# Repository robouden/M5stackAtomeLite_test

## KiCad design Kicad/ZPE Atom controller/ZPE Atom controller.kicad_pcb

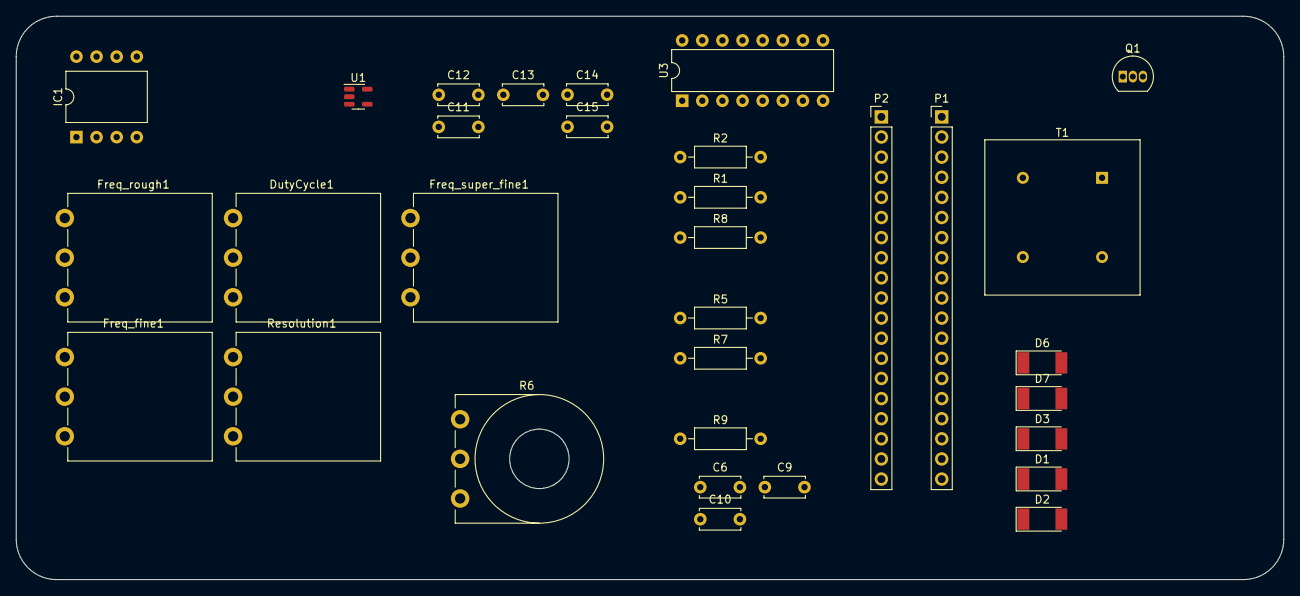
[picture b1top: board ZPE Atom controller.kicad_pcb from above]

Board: 2 copper layers, 160.0 x 71.1 mm, 32 parts (0 on the bottom side), 20 nets, no tracks yet.

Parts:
C6: 1NF 400V; C_Disc_D5.0mm_W2.5mm_P5.00mm
C9, C10, C11, C12, C13, C14, C15: 100nF; C_Disc_D5.0mm_W2.5mm_P5.00mm
D1, D2, D3: D524; D_MELF
D6, D7: 4004; D_MELF
DutyCycle1: 10k; Potentiometer_Piher_PC-16_Single_Vertical
Freq_fine1: 10K; Potentiometer_Piher_PC-16_Single_Vertical
Freq_rough1: 10K; Potentiometer_Piher_PC-16_Single_Vertical
Freq_super_fine1: 10k; Potentiometer_Piher_PC-16_Single_Vertical
IC1: TC4424AVPA; DIP-8_W10.16mm
P1, P2: CONN_01X18; PinHeader_1x19_P2.54mm_Vertical
Q1: PN2222A; TO-92_Inline
R1: 4.7k; R_Axial_DIN0207_L6.3mm_D2.5mm_P10.16mm_Horizontal
R2, R8: 1k; R_Axial_DIN0207_L6.3mm_D2.5mm_P10.16mm_Horizontal
R5: 1K; R_Axial_DIN0207_L6.3mm_D2.5mm_P10.16mm_Horizontal
R6: 100; Potentiometer_Piher_T-16L_Single_Vertical_Hole
R7, R9: 1M; R_Axial_DIN0207_L6.3mm_D2.5mm_P10.16mm_Horizontal
Resolution1: 10K; Potentiometer_Piher_PC-16_Single_Vertical
T1: Transformer_SP_1S; Transformer_NF_ETAL_P1165
U1: SSD1306; SOT-23-5
U3: 4049; DIP-16_W7.62mm

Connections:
+3V3: DutyCycle1.1, Freq_fine1.1, Freq_rough1.1, Freq_super_fine1.1, Resolution1.1, U1.2 (VCC), U3.1 (VDD), U3.16 (VCC)
+12V: IC1.6 (VDD), R6.1, R6.2
/IO12: C10.1, D7.1 (K), P1.13, R5.2
/IO14: C9.1, D6.1 (K), P1.12, R8.2
/IO21: P2.6, U1.3 (SCL)
/IO22: P2.3, U1.4 (SDA)
/IO32: C12.1, Freq_fine1.2, P1.7
/IO33: IC1.2 (IN_A), P1.8, R1.1, U3.3
/IO34: C14.1, P1.5, Resolution1.2
/IO35: C15.1, DutyCycle1.2, P1.6
/IO36: C13.1, Freq_super_fine1.2, P1.3
/IO39: C11.1, Freq_rough1.2, P1.4
GND: C9.2, C10.2, C11.2, C12.2, C13.2, C14.2, C15.2, DutyCycle1.3, Freq_fine1.3, Freq_rough1.3, Freq_super_fine1.3, IC1.3 (GND), P1.14, P2.7, Q1.1 (E), R1.2, R5.1, R8.1, Resolution1.3, U1.1 (GND), U3.8 (GND)
unnamed: D1.1 (K), T1.1 (AA)
unnamed: D2.2 (A), D3.1 (K)
unnamed: D2.1 (K), R9.1, T1.4 (SB)
unnamed: D6.2 (A), R7.2
unnamed: D7.2 (A), R9.2
unnamed: IC1.4 (IN_B), U3.2
unnamed: IC1.7 (OUT_A), R2.1

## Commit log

2021-06-19 Working M5atom lite with SSD1306 I2C
2022-01-01 Tested on SSD1306 small
2022-01-02 Update display for IN and OUT
2022-01-02 Updated display
2022-01-02 Setup button and LED
2022-01-04 PWM setup test
2022-01-04 Added analog read and led test
2022-01-04 Added Kicad files
2022-01-05 Set diplay and freq/duty/resolution
2022-01-05 Change dutyCyle
2022-01-08 Updated/creating reading dutycyle and frequency
2022-01-08 started switch case
2022-01-09 Switch case setup
2022-01-10 Updated EEPROM notes setup.
2022-01-10 Setup for WeMos Lolin32 ESP32 OLED
2022-01-12 renamed folder for ZPE hornbill
2022-01-12 Chnaged folders for hornbill
2022-01-12 Setup for Hornbill ESP32
2022-01-16 Added new Kicad files
2022-01-16 Added feq rough/fine and dutycycle functions
2022-01-16 Setup serial print changes on pots
2022-01-16 Changed outpin for driver
2022-01-17 Setup controle frequency rough and fine
2022-01-19 Modified setup
2022-01-19 Updated code
2022-01-22 Added pullup resistor for I2C
2022-01-22 Working freq generator from 1 till 39mHZ
2022-01-22 Updated version
2022-01-22 Changed pot dutycyle to freq superfine
2022-01-23 Updated schematic for 5 pots
2022-01-23 Updated code for new pots
2022-01-23 Added brightness setup
2022-01-23 Updated schematic
2022-01-24 Updated board
2022-01-25 Added 3D model for pullup
2022-01-26 added resistor for mosfet
2022-01-26 Updated transisitor driver setup
2022-01-28 Recalled code V0.96
2022-01-28 Updated with freq_base V0.96
2022-02-01 Cleaned up formating
2022-02-04 Added resistor before MOSFET
2022-02-06 added shocl 33ouH
2022-02-07 Added switches
2022-02-08 Update data from speed N-MOS FETS
2022-02-19 Added feedback measurements points
2022-02-19 Added display and output of voltage
2022-02-19 Updated display and serial reading
2022-02-19 Fixed analog read pin input
2022-02-20 Updated schematic with current limiter
2022-02-22 Updated schematic and code for analog input
2022-02-22 Changed pins for feedback to pin 16 and 17
2022-02-23 Added AC level convert on inputs
2022-02-23 Changed pins for feedback to prin 18 and 19
2022-02-23 Changed feedback pins to 12 and 14
2022-02-24 Updated to read 0 volt
2022-02-26 Changed mapping pot rough freqency
2022-02-26 Added caps to inputs of the pots.
2022-03-01 Added DC to AC inverter
2022-03-02 Display bits and start freq at 10000 HZ
2022-03-19 Updated and cleaned out the code
2022-03-29 Checked 1MHZ setup
2022-04-01 Updated files
2022-04-10 Updated schemtic
2022-04-14 Changed multiplier for freq_base to 100 ZPE at 338khz gives in coils system 3 2.2mhz nearly flat. (picture of scope later)
2022-04-15 Added hex inverter 4006 to the schematic
2022-04-17 added inverter CD4049 for inverted PWM
2022-04-17 Updated footprint cd4049
2022-04-26 Updated board inverter
2022-04-30 Test for resonance
2023-09-25 move workspace file
